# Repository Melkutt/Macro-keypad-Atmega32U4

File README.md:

This is still in progress, as usual, but it works.

Macro keypad based of a AtMega32U4AU, SK6812 backlit and Cherry key's

--------------------------------------------------------------
20250612:
I have updated the PCB now in KiCad 9 to work out a few buggs.
--------------------------------------------------------------

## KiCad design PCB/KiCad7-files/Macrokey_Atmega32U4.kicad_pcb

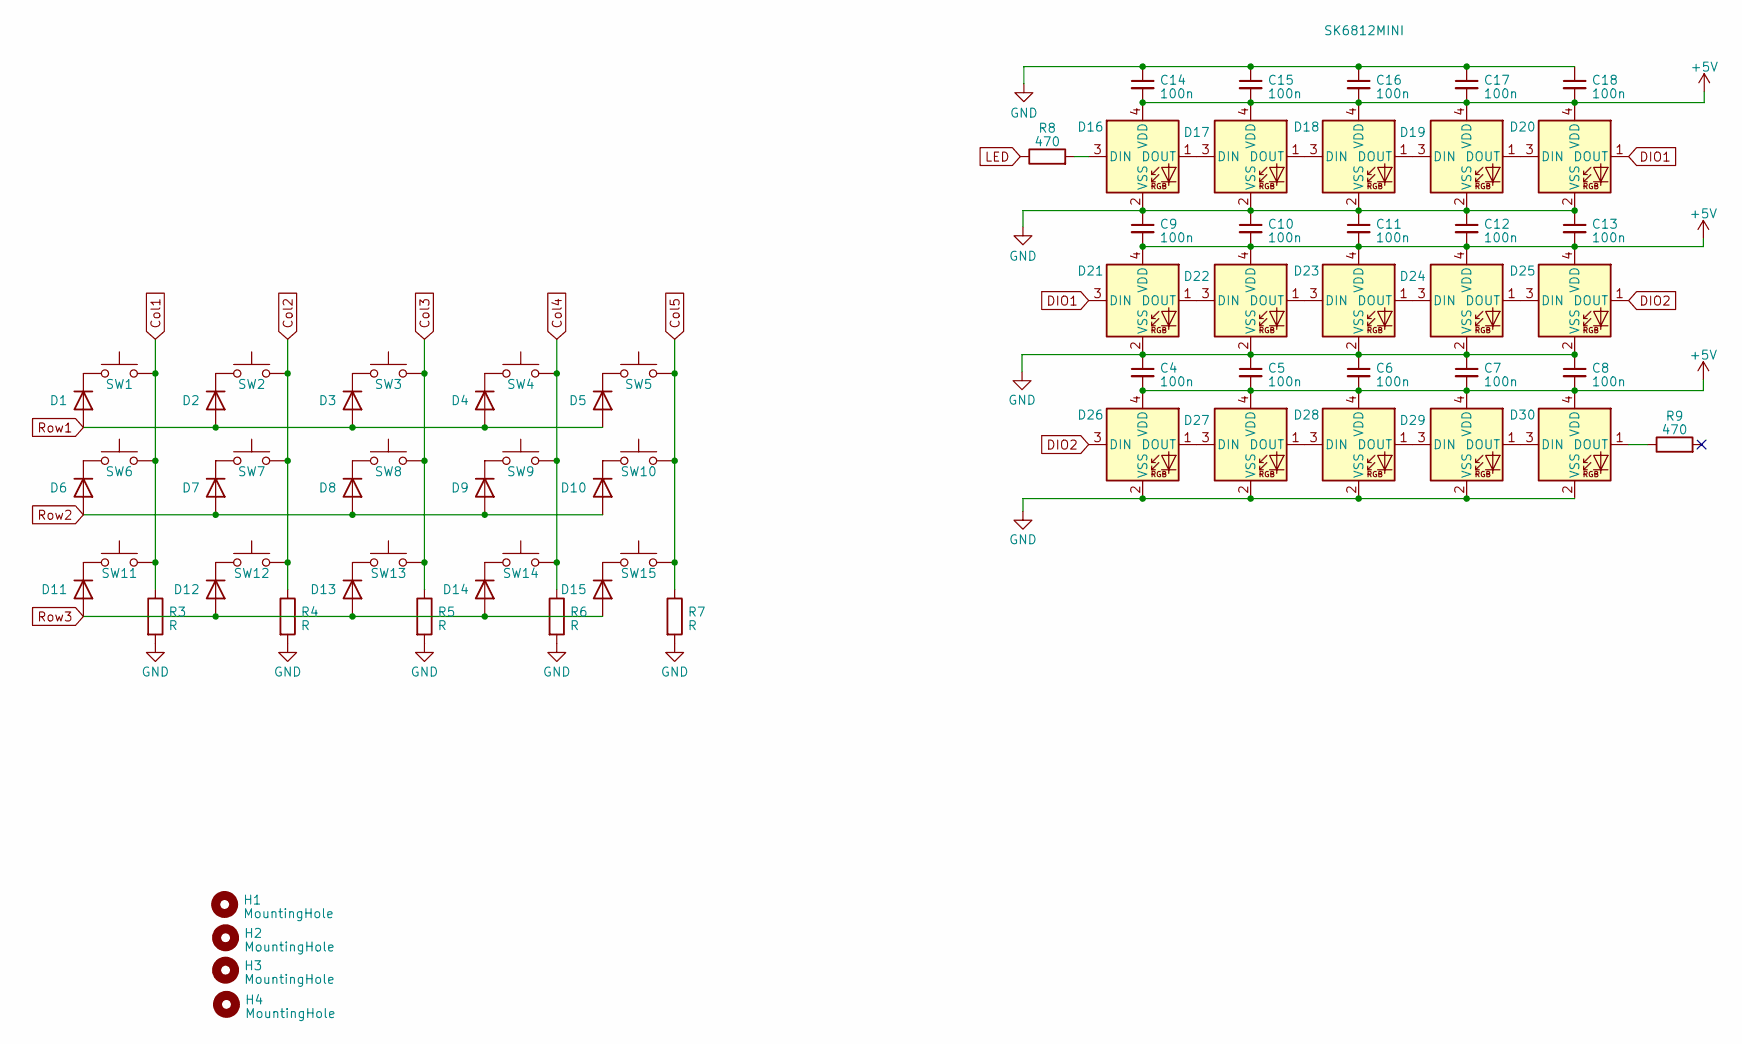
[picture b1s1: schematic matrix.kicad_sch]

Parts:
C4, C5, C6, C7, C8, C9, C10, C11, C12, C13, C14, C15, C16, C17, C18: 100n; C_0603_1608Metric_Pad1.08x0.95mm_HandSolder
D1, D2, D3, D4, D5, D6, D7, D8, D9, D10, D11, D12, D13, D14, D15: LL4448; D_MiniMELF
D16, D17, D18, D19, D20, D21, D22, D23, D24, D25, D26, D27, D28, D29, D30: SK6812MINI; LED_SK6812MINI_PLCC4_3.5x3.5mm_P1.75mm
H1, H2, H3, H4: MountingHole; MountingHole_4.3mm_M4
R3, R4, R5, R6, R7: R; R_0603_1608Metric_Pad0.98x0.95mm_HandSolder
R8, R9: 470; R_0603_1608Metric_Pad0.98x0.95mm_HandSolder
SW1, SW2, SW3, SW4, SW5, SW6, SW7, SW8, SW9, SW10, SW11, SW12, SW13, SW14, SW15: SW_Push; SW_Cherry_MX_PCB_1.00u

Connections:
+5V: C4.2, C5.2, C6.2, C7.2, C8.2, C9.2, C10.2, C11.2, C12.2, C13.2, C14.2, C15.2, C16.2, C17.2, C18.2, D16.4 (VDD), D17.4 (VDD), D18.4 (VDD), D19.4 (VDD), D20.4 (VDD), D21.4 (VDD), D22.4 (VDD), D23.4 (VDD), D24.4 (VDD), D25.4 (VDD), D26.4 (VDD), D27.4 (VDD), D28.4 (VDD), D29.4 (VDD), D30.4 (VDD); also elsewhere on the board
Col1: R3.1, SW1.2, SW6.2, SW11.2; also elsewhere on the board
Col2: R4.1, SW2.2, SW7.2, SW12.2; also elsewhere on the board
Col3: R5.1, SW3.2, SW8.2, SW13.2; also elsewhere on the board
Col4: R6.1, SW4.2, SW9.2, SW14.2; also elsewhere on the board
Col5: R7.1, SW5.2, SW10.2, SW15.2; also elsewhere on the board
DIO1: D20.1 (DOUT), D21.3 (DIN)
DIO2: D25.1 (DOUT), D26.3 (DIN)
GND: C4.1, C5.1, C6.1, C7.1, C8.1, C9.1, C10.1, C11.1, C12.1, C13.1, C14.1, C15.1, C16.1, C17.1, C18.1, D16.2 (VSS), D17.2 (VSS), D18.2 (VSS), D19.2 (VSS), D20.2 (VSS), D21.2 (VSS), D22.2 (VSS), D23.2 (VSS), D24.2 (VSS), D25.2 (VSS), D26.2 (VSS), D27.2 (VSS), D28.2 (VSS), D29.2 (VSS), D30.2 (VSS), R3.2, R4.2, R5.2, R6.2, R7.2; also elsewhere on the board
LED: R8.1; also elsewhere on the board
unnamed: D1.1 (K), SW1.1
unnamed: D2.1 (K), SW2.1
unnamed: D3.1 (K), SW3.1
unnamed: D4.1 (K), SW4.1
unnamed: D5.1 (K), SW5.1
unnamed: D6.1 (K), SW6.1
unnamed: D7.1 (K), SW7.1
unnamed: D8.1 (K), SW8.1
unnamed: D9.1 (K), SW9.1
unnamed: D10.1 (K), SW10.1
unnamed: D11.1 (K), SW11.1
unnamed: D12.1 (K), SW12.1
unnamed: D13.1 (K), SW13.1
unnamed: D14.1 (K), SW14.1
unnamed: D15.1 (K), SW15.1
unnamed: D16.3 (DIN), R8.2
unnamed: D16.1 (DOUT), D17.3 (DIN)
unnamed: D17.1 (DOUT), D18.3 (DIN)
unnamed: D18.1 (DOUT), D19.3 (DIN)
unnamed: D19.1 (DOUT), D20.3 (DIN)
unnamed: D21.1 (DOUT), D22.3 (DIN)
unnamed: D22.1 (DOUT), D23.3 (DIN)
unnamed: D23.1 (DOUT), D24.3 (DIN)
unnamed: D24.1 (DOUT), D25.3 (DIN)
unnamed: D26.1 (DOUT), D27.3 (DIN)
unnamed: D27.1 (DOUT), D28.3 (DIN)
unnamed: D28.1 (DOUT), D29.3 (DIN)
unnamed: D29.1 (DOUT), D30.3 (DIN)
unnamed: D30.1 (DOUT), R9.1
Row1: D1.2 (A), D2.2 (A), D3.2 (A), D4.2 (A), D5.2 (A); also elsewhere on the board
Row2: D6.2 (A), D7.2 (A), D8.2 (A), D9.2 (A), D10.2 (A); also elsewhere on the board
Row3: D11.2 (A), D12.2 (A), D13.2 (A), D14.2 (A), D15.2 (A); also elsewhere on the board

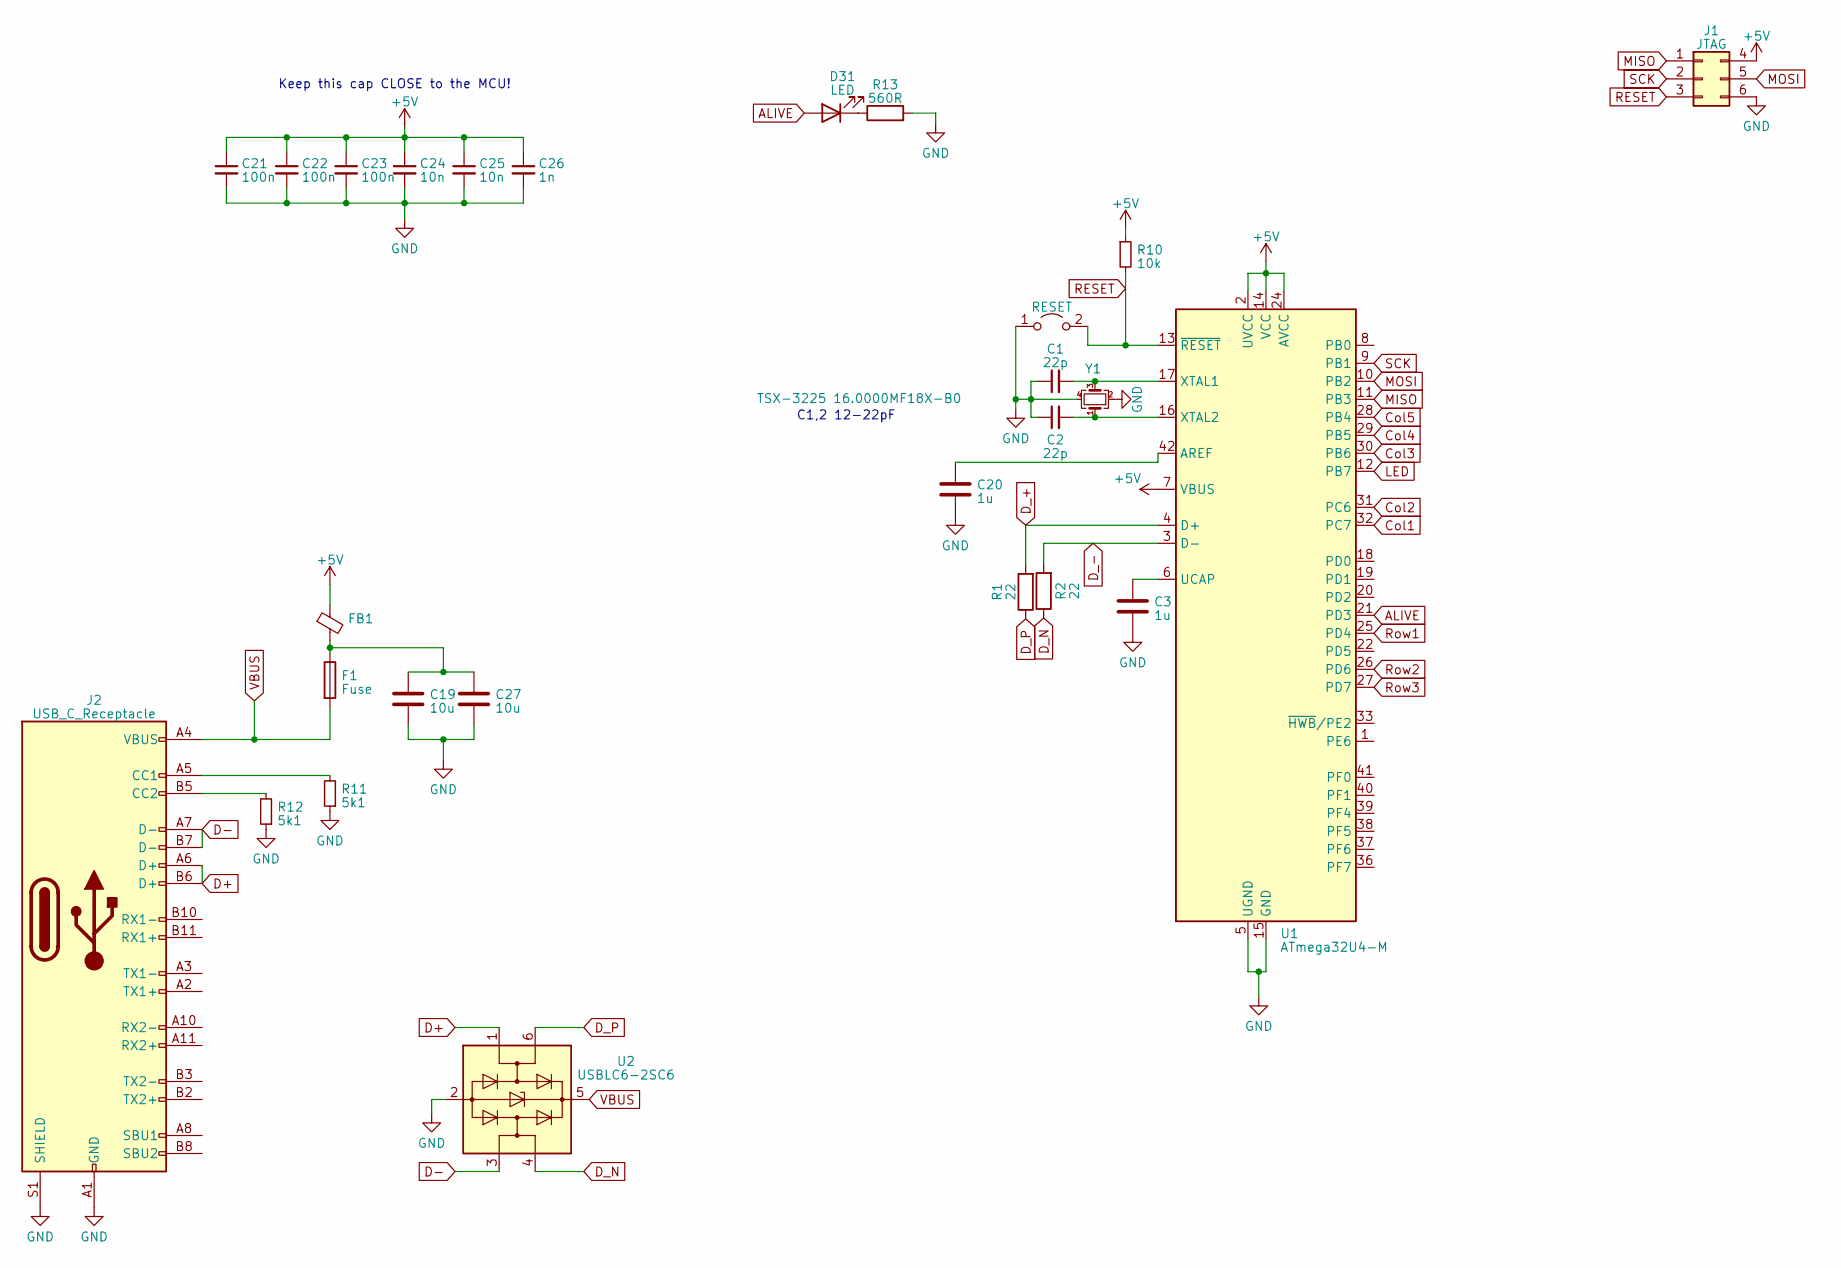
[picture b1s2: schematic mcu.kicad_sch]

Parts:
C1, C2: 22p; C_0603_1608Metric_Pad1.08x0.95mm_HandSolder
C3, C20: 1u; C_0603_1608Metric_Pad1.08x0.95mm_HandSolder
C19, C27: 10u; C_0603_1608Metric_Pad1.08x0.95mm_HandSolder
C21, C22, C23: 100n; C_0603_1608Metric_Pad1.08x0.95mm_HandSolder
C24, C25: 10n; C_0603_1608Metric_Pad1.08x0.95mm_HandSolder
C26: 1n; C_0603_1608Metric_Pad1.08x0.95mm_HandSolder
D31: LED; LED_0603_1608Metric_Pad1.05x0.95mm_HandSolder
F1: Fuse; Fuse_1206_3216Metric_Pad1.42x1.75mm_HandSolder
FB1: FerriteBead_Small; L_0603_1608Metric_Pad1.05x0.95mm_HandSolder
J1: JTAG; PinSocket_2x03_P2.54mm_Vertical
J2: USB_C_Receptacle; USB_C_Receptacle_GCT_USB4085
JP1: RESET; SolderJumper-2_P1.3mm_Open_TrianglePad1.0x1.5mm
R1, R2: 22; R_0603_1608Metric_Pad0.98x0.95mm_HandSolder
R10: 10k; R_0603_1608Metric_Pad0.98x0.95mm_HandSolder
R11, R12: 5k1; R_0603_1608Metric_Pad0.98x0.95mm_HandSolder
R13: 560R; R_0603_1608Metric_Pad0.98x0.95mm_HandSolder
U1: ATmega32U4-M; TQFP-44_10x10mm_P0.8mm
U2: USBLC6-2SC6; SOT-23-6
Y1: TSX-3225 16.0000MF18X-B0; Crystal_SMD_SeikoEpson_TSX3225-4Pin_3.2x2.5mm

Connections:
+5V: C21.1, C22.1, C23.1, C24.1, C25.1, C26.1, FB1.1, J1.4, R10.1, U1.2 (UVCC), U1.7 (VBUS), U1.14 (VCC), U1.24 (AVCC), U1.34 (VCC), U1.44 (AVCC); also elsewhere on the board
ALIVE: D31.2 (A), U1.21 (PD3)
Col1: U1.32 (PC7); also elsewhere on the board
Col2: U1.31 (PC6); also elsewhere on the board
Col3: U1.30 (PB6); also elsewhere on the board
Col4: U1.29 (PB5); also elsewhere on the board
Col5: U1.28 (PB4); also elsewhere on the board
D+: J2.A6 (D+), J2.B6 (D+), U2.1 (I/O1)
D-: J2.A7 (D-), J2.B7 (D-), U2.3 (I/O2)
D_+: R1.2, U1.4 (D+)
D_-: R2.2, U1.3 (D-)
D_N: R2.1, U2.4 (I/O2)
D_P: R1.1, U2.6 (I/O1)
GND: C1.1, C2.1, C3.2, C19.1, C20.2, C21.2, C22.2, C23.2, C24.2, C25.2, C26.2, C27.1, J1.6, J2.A1 (GND), J2.A12 (GND), J2.B1 (GND), J2.B12 (GND), J2.S1 (SHIELD), JP1.1 (A), R11.1, R12.1, R13.2, U1.5 (UGND), U1.15 (GND), U1.23 (GND), U1.35 (GND), U1.43 (GND), U1.45 (GND), U2.2 (GND), Y1.2, Y1.4; also elsewhere on the board
LED: U1.12 (PB7); also elsewhere on the board
MISO: J1.1, U1.11 (PB3)
MOSI: J1.5, U1.10 (PB2)
unnamed: C19.2, C27.2, F1.1, FB1.2
unnamed: D31.1 (K), R13.1
unnamed: J2.A5 (CC1), R11.2
unnamed: J2.B5 (CC2), R12.2
unnamed: C20.1, U1.42 (AREF)
unnamed: C3.1, U1.6 (UCAP)
unnamed: C1.2, U1.17 (XTAL1), Y1.3
unnamed: C2.2, U1.16 (XTAL2), Y1.1
RESET: J1.3, JP1.2 (B), R10.2, U1.13 (~RESET)
Row1: U1.25 (PD4); also elsewhere on the board
Row2: U1.26 (PD6); also elsewhere on the board
Row3: U1.27 (PD7); also elsewhere on the board
SCK: J1.2, U1.9 (PB1)
VBUS: F1.2, J2.A4 (VBUS), J2.A9 (VBUS), J2.B4 (VBUS), J2.B9 (VBUS), U2.5 (VBUS)

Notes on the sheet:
Keep this cap CLOSE to the MCU!
C1,2 12-22pF

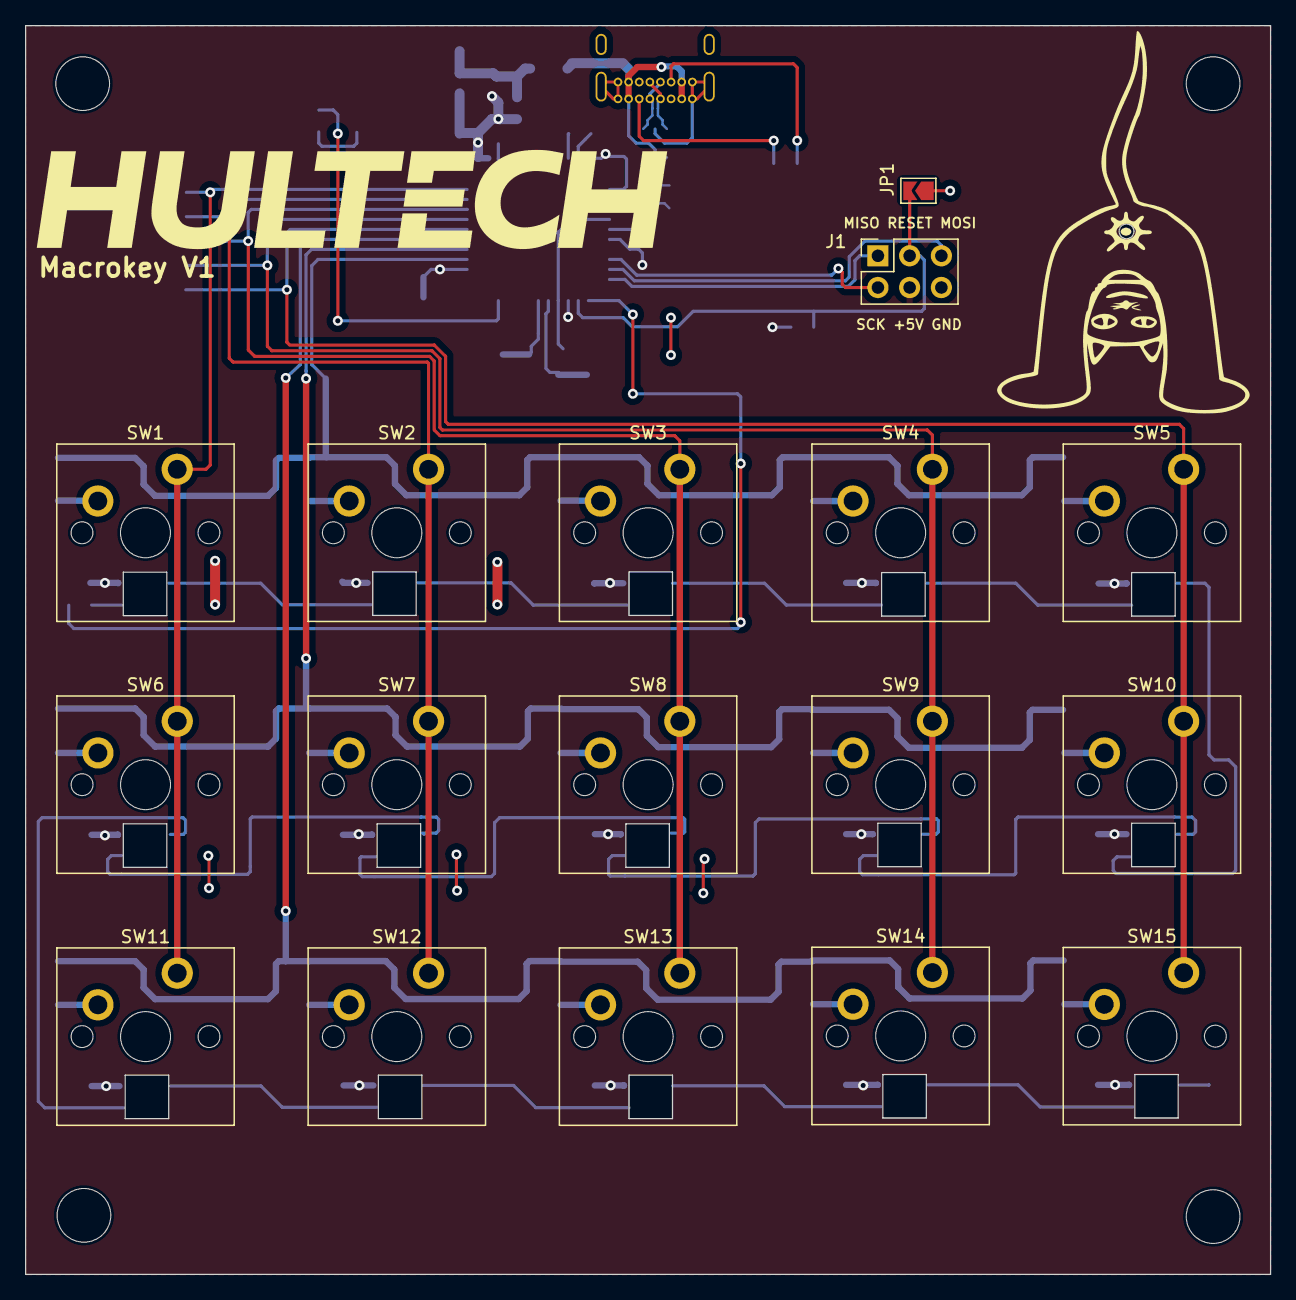
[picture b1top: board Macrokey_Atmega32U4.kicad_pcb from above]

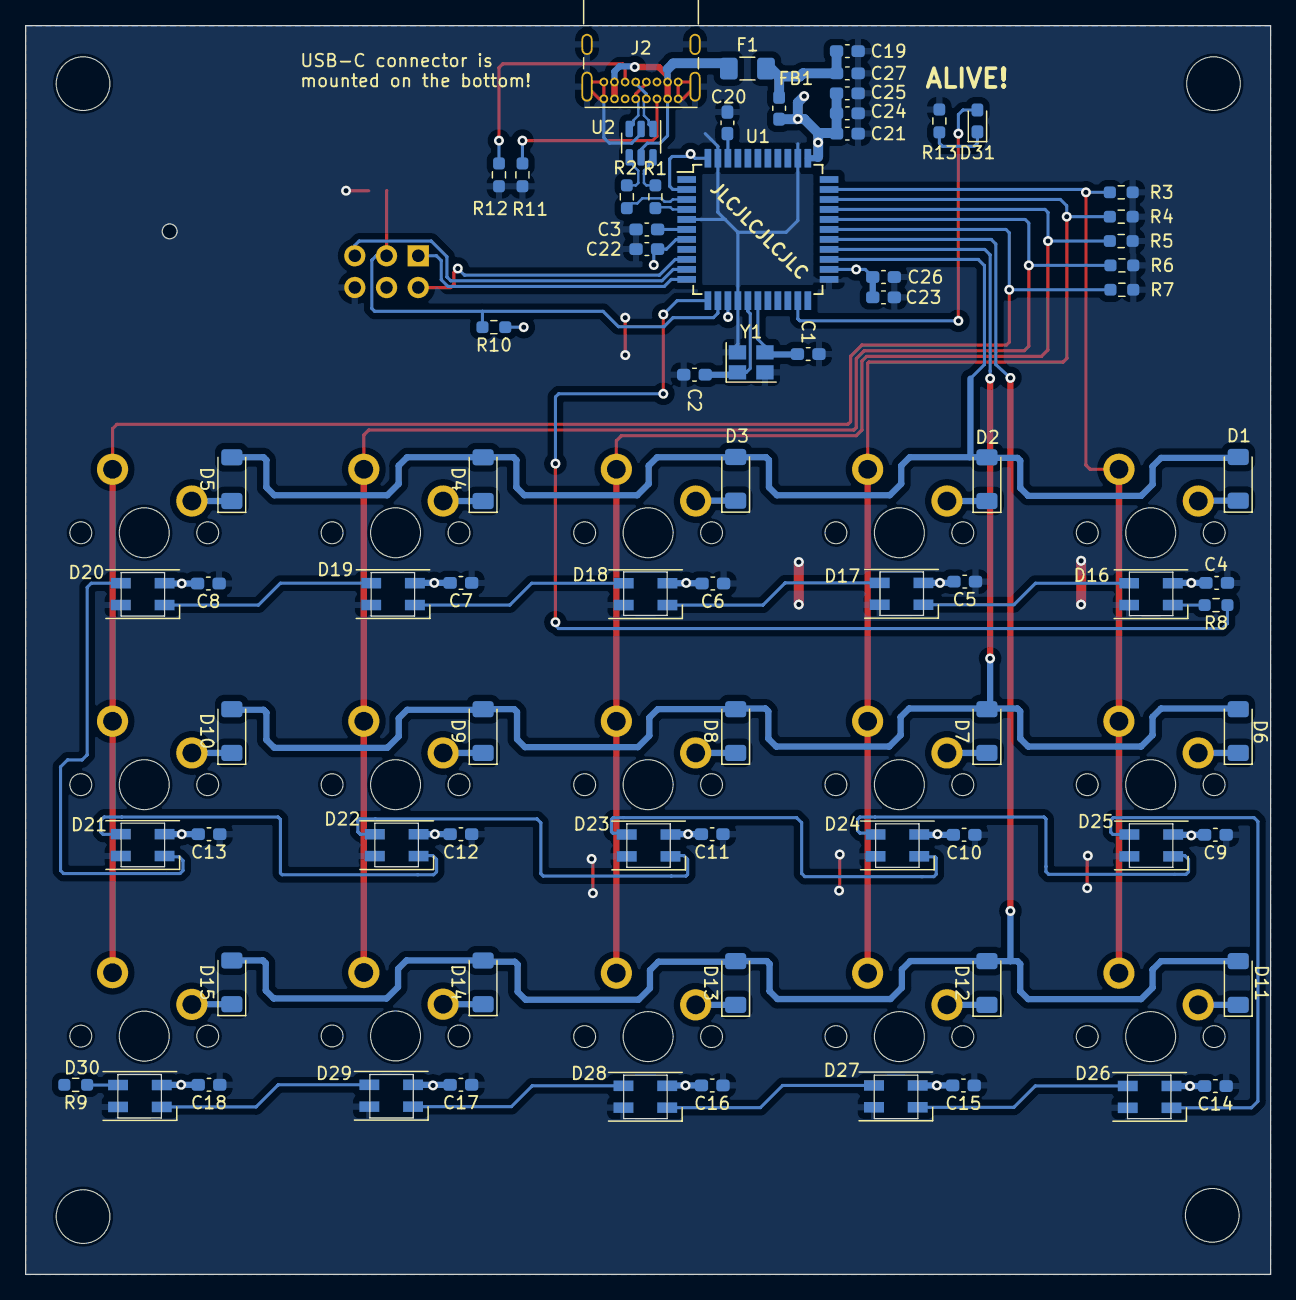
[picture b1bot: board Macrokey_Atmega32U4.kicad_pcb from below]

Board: 2 copper layers, 99.7 x 100.0 mm, 98 parts (77 on the bottom side), 62 nets.

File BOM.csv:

"Reference","Qty","Value","DNP","Exclude from BOM","Exclude from Board","Footprint","Datasheet"
"C1,C2","2","22p","","","","Capacitor_SMD:C_0603_1608Metric_Pad1.08x0.95mm_HandSolder","~"
"C3,C20","2","1u","","","","Capacitor_SMD:C_0603_1608Metric_Pad1.08x0.95mm_HandSolder","~"
"C4,C5,C6,C7,C8,C9,C10,C11,C12,C13,C14,C15,C16,C17,C18,C21,C22,C23","18","100n","","","","Capacitor_SMD:C_0603_1608Metric_Pad1.08x0.95mm_HandSolder","~"
"C19,C27","2","10u","","","","Capacitor_SMD:C_0603_1608Metric_Pad1.08x0.95mm_HandSolder","~"
"C24,C25","2","10n","","","","Capacitor_SMD:C_0603_1608Metric_Pad1.08x0.95mm_HandSolder","~"
"C26","1","1n","","","","Capacitor_SMD:C_0603_1608Metric_Pad1.08x0.95mm_HandSolder","~"
"D1,D2,D3,D4,D5,D6,D7,D8,D9,D10,D11,D12,D13,D14,D15","15","LL4448","","","","Diode_SMD:D_MiniMELF","http://www.vishay.com/docs/85557/ll4148.pdf"
"D16,D17,D18,D19,D20,D21,D22,D23,D24,D25,D26,D27,D28,D29,D30","15","SK6812MINI","","","","LED_SMD:LED_SK6812MINI_PLCC4_3.5x3.5mm_P1.75mm","https://cdn-shop.adafruit.com/product-files/2686/SK6812MINI_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"
"D31","1","LED","","","","LED_SMD:LED_0603_1608Metric_Pad1.05x0.95mm_HandSolder","~"
"F1","1","Fuse","","","","Fuse:Fuse_1206_3216Metric_Pad1.42x1.75mm_HandSolder","~"
"FB1","1","FerriteBead_Small","","","","Inductor_SMD:L_0603_1608Metric_Pad1.05x0.95mm_HandSolder","~"
"H1,H2,H3,H4","4","MountingHole","","","","MountingHole:MountingHole_4.3mm_M4","~"
"J1","1","JTAG","","","","Connector_PinSocket_2.54mm:PinSocket_2x03_P2.54mm_Vertical","~"
"J2","1","USB_C_Receptacle","","","","Connector_USB:USB_C_Receptacle_GCT_USB4085","https://www.usb.org/sites/default/files/documents/usb_type-c.zip"
"R1,R2","2","22","","","","Resistor_SMD:R_0603_1608Metric_Pad0.98x0.95mm_HandSolder","~"
"R3,R4,R5,R6,R7","5","R","","","","Resistor_SMD:R_0603_1608Metric_Pad0.98x0.95mm_HandSolder","~"
"R8,R9","2","470","","","","Resistor_SMD:R_0603_1608Metric_Pad0.98x0.95mm_HandSolder","~"
"R10","1","10k","","","","Resistor_SMD:R_0603_1608Metric_Pad0.98x0.95mm_HandSolder","~"
"R11,R12","2","5k1","","","","Resistor_SMD:R_0603_1608Metric_Pad0.98x0.95mm_HandSolder","~"
"R13","1","560R","","","","Resistor_SMD:R_0603_1608Metric_Pad0.98x0.95mm_HandSolder","~"
"SW1,SW2,SW3,SW4,SW5,SW6,SW7,SW8,SW9,SW10,SW11,SW12,SW13,SW14,SW15","15","SW_Push","","","","PCM_Switch_Keyboard_Cherry_MX:SW_Cherry_MX_PCB_1.00u","~"
"SW17","1","SW_DIP_x01","","","","Button_Switch_SMD:SW_Push_1P1T_NO_CK_KSC7xxJ","~"
"U1","1","ATmega32U4-M","","","","Package_QFP:TQFP-44_10x10mm_P0.8mm","http://ww1.microchip.com/downloads/en/DeviceDoc/Atmel-7766-8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"
"U2","1","USBLC6-2SC6","","","","Package_TO_SOT_SMD:SOT-23-6","https://www.st.com/resource/en/datasheet/usblc6-2.pdf"
"Y1","1","TSX-3225 16.0000MF18X-B0","","","","Crystal:Crystal_SMD_SeikoEpson_TSX3225-4Pin_3.2x2.5mm","~"

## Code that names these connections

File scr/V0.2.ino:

#include <Adafruit_NeoMatrix.h>
#include "Adafruit_Keypad.h"

#define PIN       11 //LED pin
#define NUMPIXELS 15

const byte ROWS = 5; // rows
const byte COLS = 3; // columns

//define the symbols on the buttons of the keypads
char keys[ROWS][COLS] = {
  {'A','2','B'},
  {'4','5','6'},
  {'7','8','9'},
  {'10','11','12'},
  {'13','14','15'}
};

//byte rowPins[ROWS] = {PD4, PD5, PD7}; //connect to the row pinouts of the keypad
//byte colPins[COLS] = {PC7, PC6, PB6, PB5, PB4}; //connect to the column pinouts of the keypad

byte rowPins[ROWS] = {13, 5, 10, 9, 8}; //connect to the row pinouts of the keypad
byte colPins[COLS] = {4, 12, 6}; //connect to the column pinouts of the keypad

//initialize an instance of class NewKeypad
Adafruit_Keypad customKeypad = Adafruit_Keypad( makeKeymap(keys), rowPins, colPins, ROWS, COLS);

unsigned char randNumber;

Adafruit_NeoPixel pixels(NUMPIXELS, PIN, NEO_GRB + NEO_KHZ800);
#define DELAYVAL 1

void setup() {

  Serial.begin(115200);
/*
  pinMode(4, INPUT_PULLUP);
  pinMode(5, INPUT_PULLUP);
  pinMode(6, INPUT_PULLUP);
  pinMode(8, INPUT);
  pinMode(9, INPUT);
  pinMode(10, INPUT);
  pinMode(12, INPUT_PULLUP);
  pinMode(PC7, INPUT);  
*/
  pixels.begin();
  randomSeed(analogRead(38));
  pixels.setBrightness(10);

  customKeypad.begin();

   
}

void loop() {

  ledMatrix();
//  Serial.println("TEST");

  customKeypad.tick();

  while(customKeypad.available()){
    keypadEvent e = customKeypad.read();
    Serial.print((char)e.bit.KEY);
    if(e.bit.EVENT == KEY_JUST_PRESSED) Serial.println(" pressed");
    else if(e.bit.EVENT == KEY_JUST_RELEASED) Serial.println(" released");
    delay(10);
  }

  delay(10);


}


void ledMatrix() {

//  for(int i=0; i<NUMPIXELS; i++) {
  for(int i=random(0, 15); i<NUMPIXELS; i++) {

    
    randNumber = random(0, 255); //To adjust the color span

    pixels.setPixelColor(i, pixels.Color(random(), random(), random())); //Random colors

    pixels.show();

    //Serial.println(randNumber);  //Just for debugging!
    
    delay(DELAYVAL);

    return;

  }  


}

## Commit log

2023-07-21 Create Exemple
2023-07-22 Add files via upload
    LED and key inputs works.
2023-07-22 Create Pic
2023-07-22 Create Play with this
2025-06-12 Create KiCad_9
2025-06-12 /Exempe
